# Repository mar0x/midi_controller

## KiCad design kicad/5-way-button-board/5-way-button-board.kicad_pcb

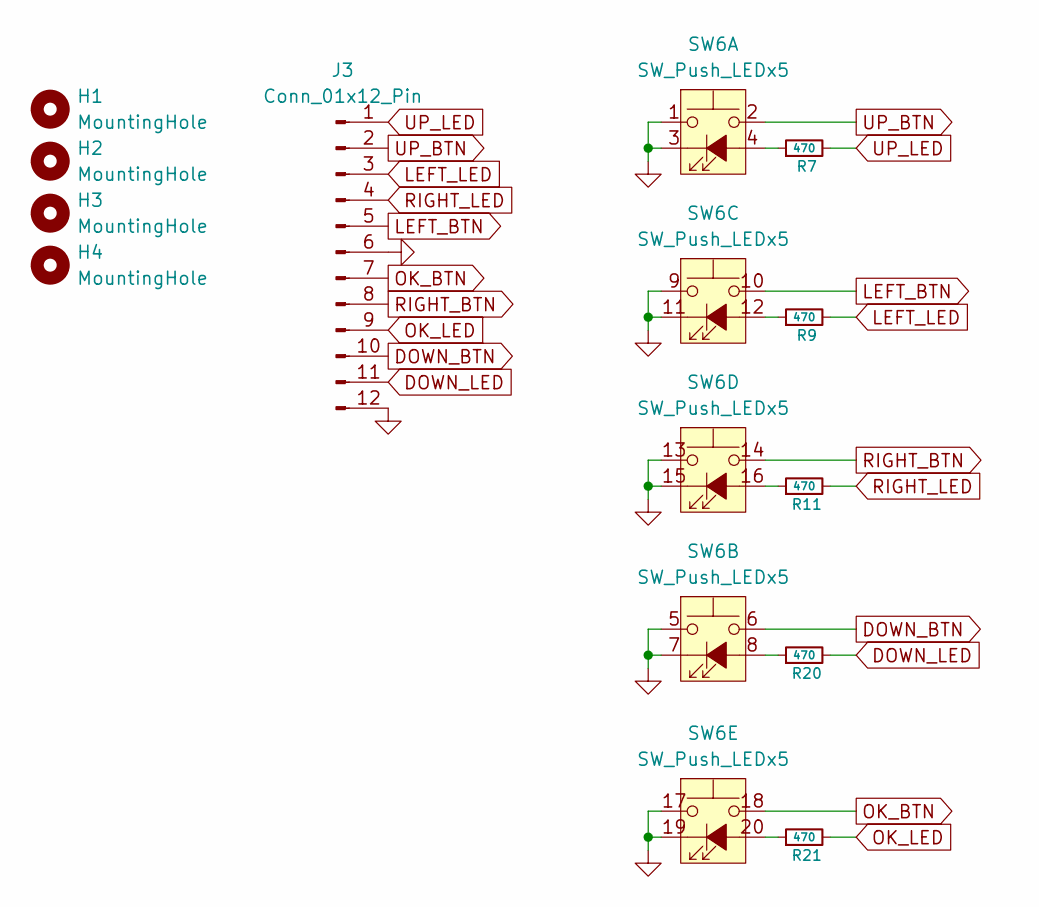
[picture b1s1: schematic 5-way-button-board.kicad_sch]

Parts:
H1, H2, H3, H4: MountingHole; MountingHole_3.2mm_M3_DIN965
J3: Conn_01x12_Pin; PinHeader_1x12_P2.54mm_Vertical
R7, R9, R11, R20, R21: 470; R_0805_2012Metric_Pad1.20x1.40mm_HandSolder
SW6: SW_Push_LEDx5; SW_PUSH_12mm_LEDx5

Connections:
DOWN_BTN: J3.10, SW6.6
DOWN_LED: J3.11, R20.2
GND: J3.6, J3.12, SW6.1, SW6.3 (K), SW6.5, SW6.7 (K), SW6.9, SW6.11 (K), SW6.13, SW6.15 (K), SW6.17, SW6.19 (K)
LEFT_BTN: J3.5, SW6.10
LEFT_LED: J3.3, R9.2
unnamed: R7.1, SW6.4 (A)
unnamed: R20.1, SW6.8 (A)
unnamed: R9.1, SW6.12 (A)
unnamed: R11.1, SW6.16 (A)
unnamed: R21.1, SW6.20 (A)
OK_BTN: J3.7, SW6.18
OK_LED: J3.9, R21.2
RIGHT_BTN: J3.8, SW6.14
RIGHT_LED: J3.4, R11.2
UP_BTN: J3.2, SW6.2
UP_LED: J3.1, R7.2

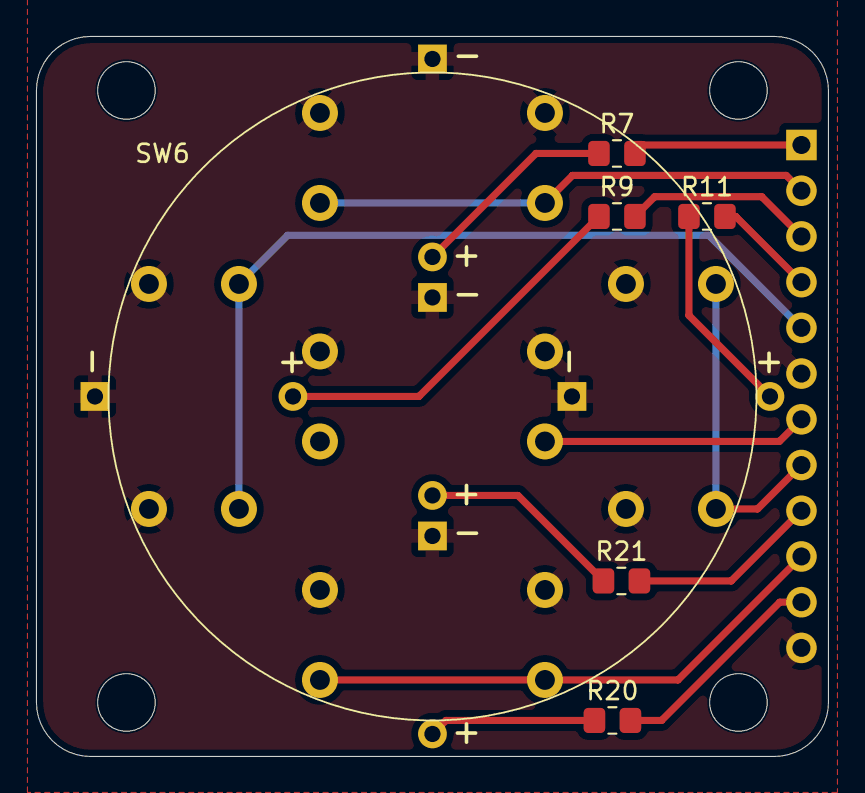
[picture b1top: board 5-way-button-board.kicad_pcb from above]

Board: 2 copper layers, 44.0 x 40.0 mm, 11 parts (1 on the bottom side), 16 nets.

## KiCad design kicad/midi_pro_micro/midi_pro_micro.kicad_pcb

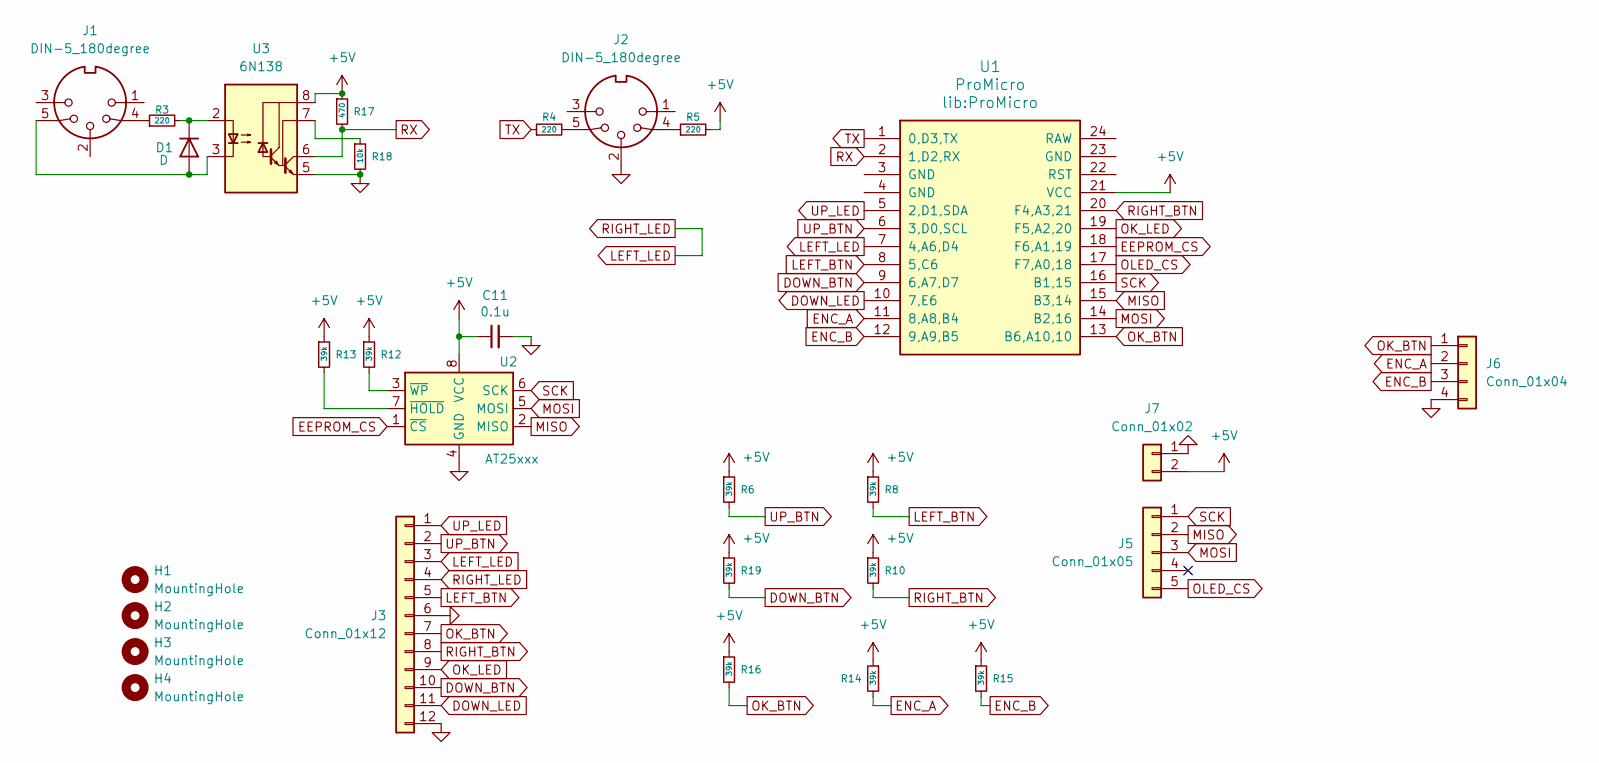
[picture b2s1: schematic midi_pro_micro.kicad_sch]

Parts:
C11: 0.1u; C_0805_2012Metric
D1: D; D_SOD-323_HandSoldering
H1, H2, H3, H4: MountingHole; MountingHole_3.2mm_M3_DIN965
J1, J2: DIN-5_180degree; DIN5MIDI-OOTDTY
J3: Conn_01x12; SW_PUSH_12mm_LEDx5_BOARD
J5: Conn_01x05; JST_PH_B5B-PH-K_1x05_P2.00mm_Vertical
J6: Conn_01x04; Encoder_BOARD-30x40
J7: Conn_01x02; JST_PH_B2B-PH-K_1x02_P2.00mm_Vertical
R3, R4, R5: 220; R_0805_2012Metric_Pad1.20x1.40mm_HandSolder
R6, R8, R10, R12, R13, R14, R15, R16, R19: 39k; R_0805_2012Metric_Pad1.20x1.40mm_HandSolder
R17: 470; R_0805_2012Metric_Pad1.20x1.40mm_HandSolder
R18: 10k; R_0805_2012Metric_Pad1.20x1.40mm_HandSolder
U1: ProMicro
U2: AT25xxx; SO-8_3.9x4.9mm_P1.27mm
U3: 6N138; DIP-8_W7.62mm_Socket

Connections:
+5V: C11.1, J7.2, R5.2, R6.1, R8.1, R10.1, R12.1, R13.1, R14.1, R15.1, R16.1, R17.1, R19.1, U1.21 (VCC), U2.8 (VCC), U3.8 (VCC)
DOWN_BTN: J3.10, R19.2, U1.9 (6,A7,D7)
DOWN_LED: J3.11, U1.10 (7,E6)
EEPROM_CS: U1.18 (F6,A1,19), U2.1 (~CS)
ENC_A: J6.2, R14.2, U1.11 (8,A8,B4)
ENC_B: J6.3, R15.2, U1.12 (9,A9,B5)
GND: C11.2, J2.2, J3.6, J3.12, J6.4, J7.1, R18.2, U2.4 (GND), U3.5 (GND)
LEFT_BTN: J3.5, R8.2, U1.8 (5,C6)
LEFT_LED: J3.3, J3.4, U1.7 (4,A6,D4)
MISO: J5.2, U1.15 (B3,14), U2.2 (MISO)
MOSI: J5.3, U1.14 (B2,16), U2.5 (MOSI)
unnamed: D1.2 (A), J1.5, U3.3 (C2)
unnamed: D1.1 (K), R3.2, U3.2 (C1)
unnamed: J1.4, R3.1
unnamed: J2.4, R5.1
unnamed: J2.5, R4.2
unnamed: R13.2, U2.7 (~HOLD)
unnamed: R12.2, U2.3 (~WP)
unnamed: R18.1, U3.7 (VO1)
OK_BTN: J3.7, J6.1, R16.2, U1.13 (B6,A10,10)
OK_LED: J3.9, U1.19 (F5,A2,20)
OLED_CS: J5.5, U1.17 (F7,A0,18)
RIGHT_BTN: J3.8, R10.2, U1.20 (F4,A3,21)
RX: R17.2, U1.2 (1,D2,RX), U3.6 (VO2)
SCK: J5.1, U1.16 (B1,15), U2.6 (SCK)
TX: R4.1, U1.1 (0,D3,TX)
UP_BTN: J3.2, R6.2, U1.6 (3,D0,SCL)
UP_LED: J3.1, U1.5 (2,D1,SDA)

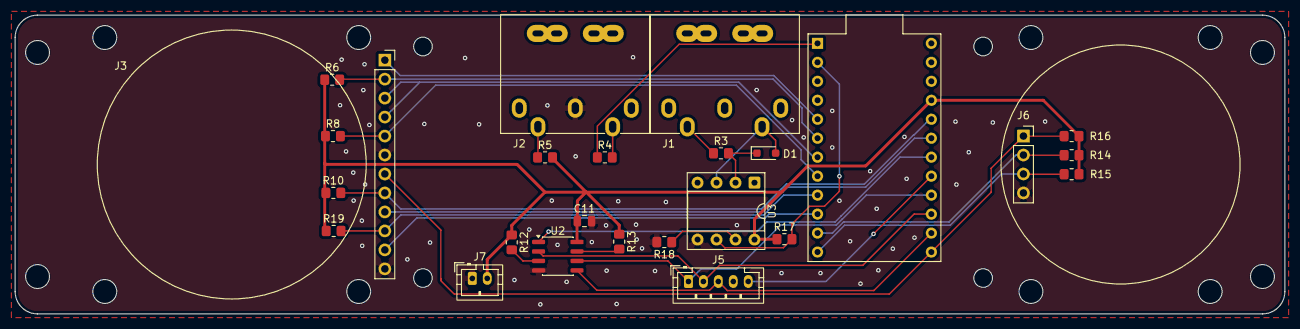
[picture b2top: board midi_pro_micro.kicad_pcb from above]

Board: 2 copper layers, 170.0 x 40.0 mm, 30 parts (0 on the bottom side), 28 nets.

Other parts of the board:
H11: Conn_01x16_Pin; OLED_1602_mechanical

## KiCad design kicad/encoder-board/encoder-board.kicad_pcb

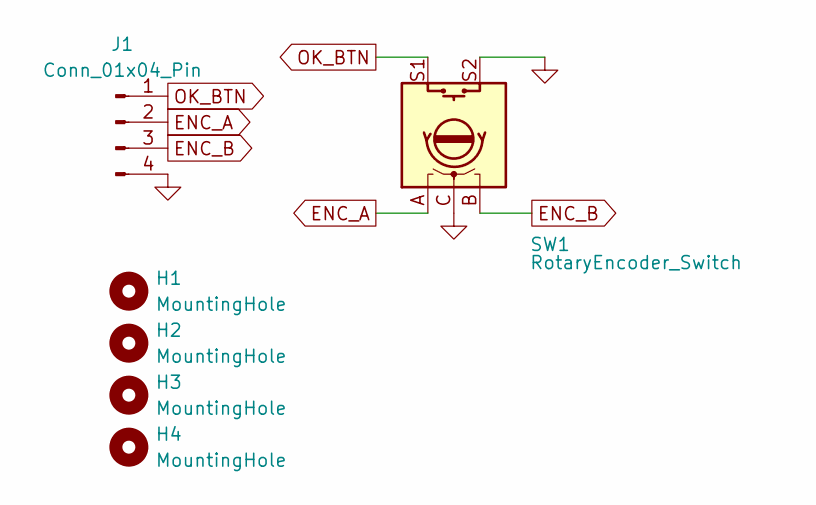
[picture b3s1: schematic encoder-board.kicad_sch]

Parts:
H1, H2, H3, H4: MountingHole; MountingHole_3.2mm_M3_DIN965
J1: Conn_01x04_Pin; PinHeader_1x04_P2.54mm_Vertical
SW1: RotaryEncoder_Switch; RotaryEncoder_Bourns_Vertical_PEC12R-3x17F-Sxxxx

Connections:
ENC_A: J1.2, SW1.A
ENC_B: J1.3, SW1.B
GND: J1.4, SW1.C, SW1.S2
OK_BTN: J1.1, SW1.S1

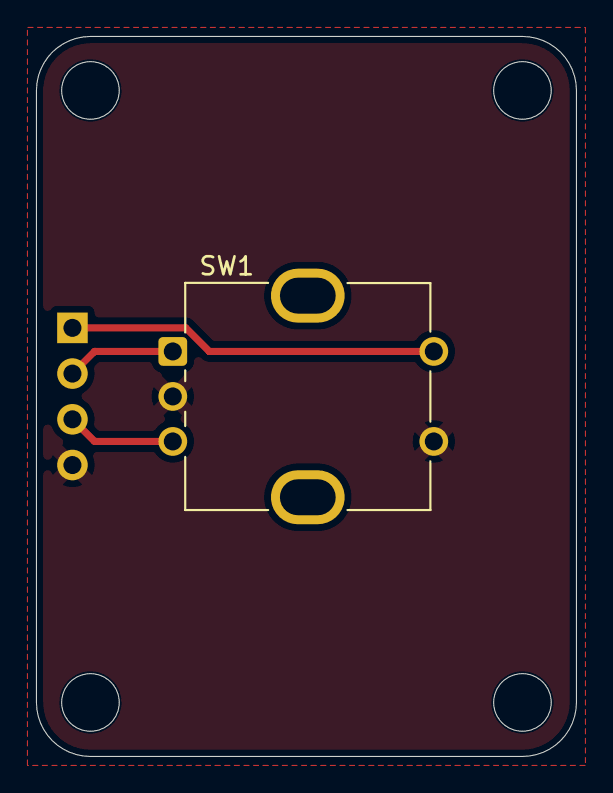
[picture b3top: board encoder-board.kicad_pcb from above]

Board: 2 copper layers, 30.0 x 40.0 mm, 6 parts (1 on the bottom side), 4 nets.

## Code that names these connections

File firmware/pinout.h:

#pragma once

#include "artl/digital_out.h"
#include "artl/digital_in.h"
#include "artl/digital_pin.h"
#include "artl/active_traits.h"

namespace midi_controller {

using spi_mosi = artl::digital_out<artl::port::B, 1>;
using spi_sck = artl::digital_out<artl::port::B, 2>;
using spi_miso = artl::digital_in<artl::port::B, 3>;
using spi_ss = artl::digital_out<artl::port::B, 0>;

using right_btn_pin = artl::digital_in<artl::port::F, 4>; // PF4 (21/A3)
using ok_btn_pin = artl::digital_in<artl::port::B, 6>; // PB6 (10/A10)
using up_btn_pin = artl::digital_in<artl::port::D, 0>; // PD0 (3)
using left_btn_pin = artl::digital_in<artl::port::C, 6>; // PC6 (5)
using down_btn_pin = artl::digital_in<artl::port::D, 7>; // PD7 (6/A7)
using enc_a_pin = artl::digital_in<artl::port::B, 4>; // PB4 (8/A8)
using enc_b_pin = artl::digital_in<artl::port::B, 5>; // PB5 (9/A9)

using ok_led_pin = artl::digital_out<artl::port::F, 5>; // PF5 (20/A2)
using up_led_pin = artl::digital_out<artl::port::D, 1>; // PD1 (2)
using left_led_pin = artl::digital_out<artl::port::D, 4>; // PD4 (4/A6)
using down_led_pin = artl::digital_out<artl::port::E, 6>; // PE6 (7)

using eeprom_cs_pin = artl::digital_pin<artl::port::F, 6>; // PF6 (19/A1)
using oled_cs_pin = artl::digital_pin<artl::port::F, 7>; // PF7 (18/A0)

using eeprom_cs = artl::active_low<eeprom_cs_pin>;
using oled_cs = artl::active_low<oled_cs_pin>;

}

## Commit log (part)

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2026-04-11 Starting MIDI controller board
2026-04-12 Draft schematic
2026-04-15 Removing MIDI IN
2026-05-21 Add MIDI IN once again
2026-05-24 Add 5-way button symbol
2026-05-25 5-way-button board
2026-05-26 Add encoder board
2026-05-26 Add 2.42 OLED display
2026-05-27 Add case body prototype
2026-05-28 Basic layout ready
2026-05-28 Start PCB trace
2026-05-28 PCB trace finished
2026-05-29 Boards fabrication
2026-06-15 Start working on firmware
2026-06-20 Encoder improvements
2026-06-21 Keep working on firmware
2026-06-23 Still working on firmware
2026-06-24 Add Mobius documents
2026-06-24 JS notes
2026-06-28 Mobius program switch
2026-06-28 Start client
2026-06-29 Basic port support
2026-06-29 Basic table
